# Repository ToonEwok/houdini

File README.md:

The Houdini is a drop-in mixbox conversion for fight sticks with ~23.5MM holes for said stick (sanwa or hori will work off the top of my head).

### Note:  
As of May 26, 2025 I am yet to get the PCB's printed and tested, if I would've known I was going to make this I would've waited before placing my order with the pcb manufacturer. At any rate this is your disclaimer that this has not technically been tested only test fit, however I am 99.9% sure it will work and will be ordering a small batch the next time I place an order for a bigger personal project I currently have.

To assemble you will need:

- 1x PCB  
- ~37 grams of the filament of your choice for the following parts:  
  - 1x houdini_top  
  - 1x houdini_base  
  - 1x houdini_screw  
- 4x choc v1 switches  
- 4x choc v1 hotswaps (PG1350)  
- 6x M2x4MM screws  
- 6x M2 brass inserts, the dimensions of the ones I used are M2x3x3.5  
- Really any wire, 22 AWG is the typical gauge for fight sticks  

Lastly, if you are using this to plug directly into an existing wiring harness I recommend getting a female 2.54 pitch 5 pin connector and some 2.54 male-to-male pins (something like these - https://www.digikey.com/en/products/detail/harwin-inc/D01-9923246/3918909) that should allow you to plug into your existing harness with no issue.

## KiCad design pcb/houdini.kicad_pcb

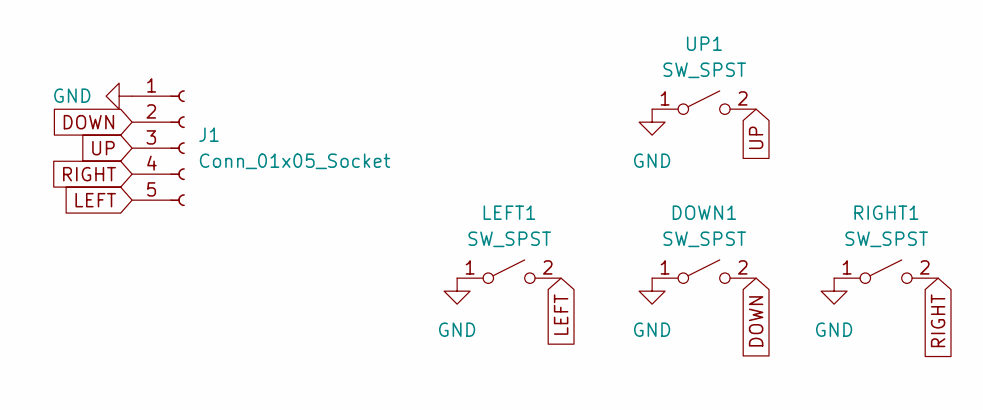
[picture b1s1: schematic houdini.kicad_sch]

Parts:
DOWN1: SW_SPST; Kailh_socket_PG1350
J1: Conn_01x05_Socket; PinSocket_1x05_P2.54mm_Vertical
LEFT1: SW_SPST; Kailh_socket_PG1350
RIGHT1: SW_SPST; Kailh_socket_PG1350
UP1: SW_SPST; Kailh_socket_PG1350

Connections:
DOWN: DOWN1.2 (B), J1.2
GND: DOWN1.1 (A), J1.1, LEFT1.1 (A), RIGHT1.1 (A), UP1.1 (A)
LEFT: J1.5, LEFT1.2 (B)
RIGHT: J1.4, RIGHT1.2 (B)
UP: J1.3, UP1.2 (B)

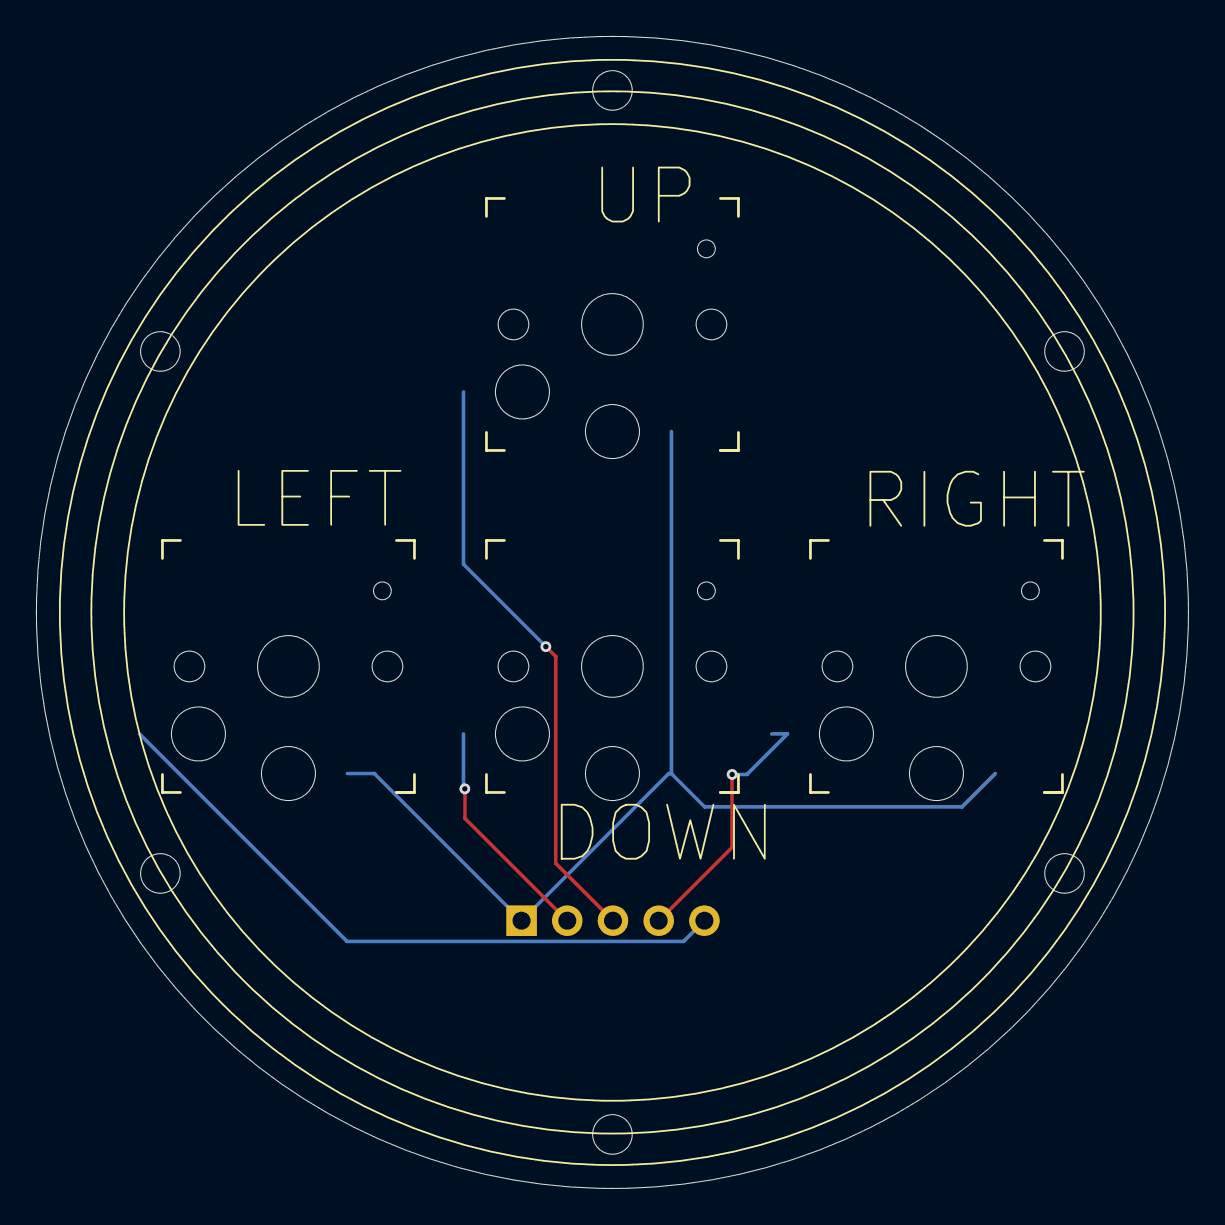
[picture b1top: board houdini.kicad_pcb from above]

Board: 2 copper layers, 64.0 x 64.0 mm, 5 parts (1 on the bottom side), 5 nets.

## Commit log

2025-05-26 first push with all core files
2025-05-27 fixed formatting for README.md
2025-05-27 removed autosave file
